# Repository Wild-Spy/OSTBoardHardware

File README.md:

# Open Source Timer Board Hardware
#### Rev 1.1

This repository contains the design for the Open Source Timer board.

These files were created in [KiCad](http://kicad-pcb.org/) 

Rev 1.1 contains
 - Schematic
 - PCB
 - Gerbers
 - BOM
 - PnP File
 - Renders
 - Libs
 - 3D Models

### Latest Version
Latest version is [Rev1.1](https://github.com/Wild-Spy/OSTBoardHardware/tree/rev1.1).  See that tag for more info.

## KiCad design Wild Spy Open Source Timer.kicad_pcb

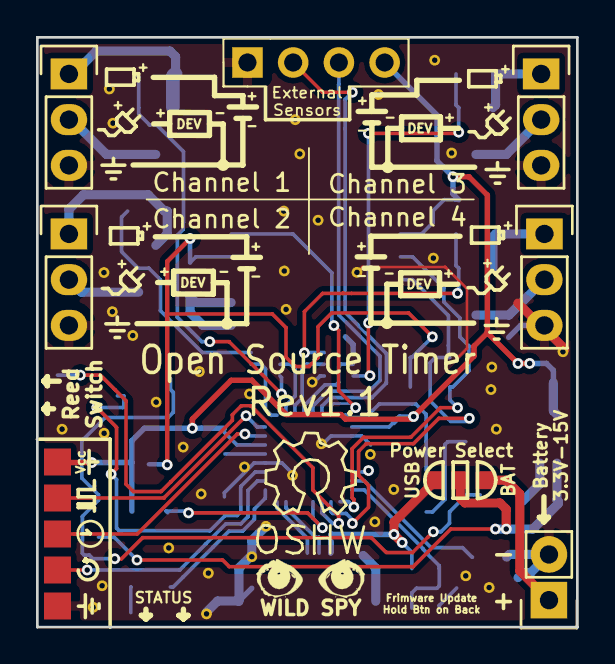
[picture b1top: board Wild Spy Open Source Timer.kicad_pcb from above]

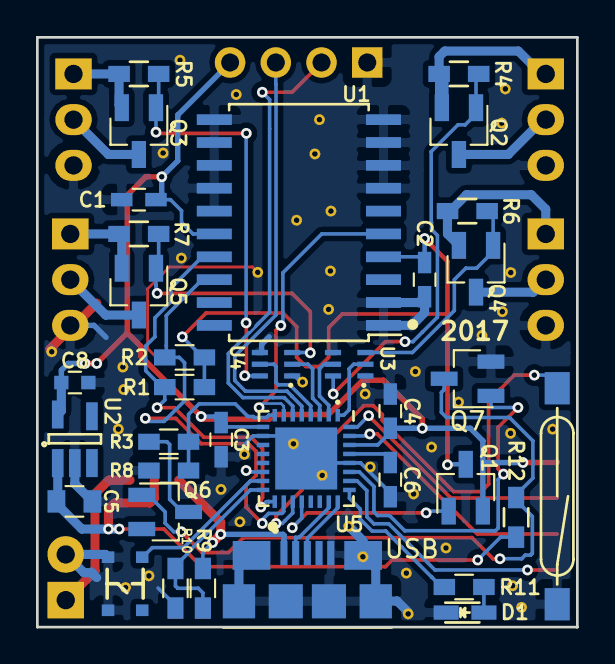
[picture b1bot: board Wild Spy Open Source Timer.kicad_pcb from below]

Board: 2 copper layers, 30.0 x 32.8 mm, 43 parts (35 on the bottom side), 43 nets.

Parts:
Battery1: CONN_01X02; Pin_Header_Straight_1x02
C1, C2, C3, C4: 0.1uF; C_0603_HandSoldering
C5: CL10A105KB8NNNC; C_0805
C6: 1uF; C_0603_HandSoldering
C8: CL10B225KQ8NFNC; C_0603
CH1, CH2, CH3, CH4: CONN_01X03; Pin_Header_Straight_1x03
D1: LED; LED_0603
JP1: JUMPER3; SOLDER-JUMPER_2-WAY
PBus1: CONN_01X04; Pin_Header_Straight_1x04_Pitch2.54mm
Q1, Q2, Q3, Q4, Q5, Q6: AO3415; SOT-23-HandSoldering
Q7: BSH103; SOT-23-HandSoldering
R1, R2, R8: 10k; R_0603_HandSoldering
R3: 150k; R_0603_HandSoldering
R4, R5, R6, R7, R12: 100k; R_0603_HandSoldering
R9, R11: 1k; R_0603_HandSoldering
R10: 2k; R_0603_HandSoldering
SW1: SW_PUSH; KMT071NGJLHS_3x2.6mm_switch
SW2: ORD213; ORD213S-1
SWD1: CONN_01X05; SWD_PROG_HEADER_L
U1: DS3232SN; SOIC-20_7.5x12.8mm_Pitch1.27mm
U2: TPS70933DBVR; SOT-23-5_HandSoldering
U3, U4: UM6K33N; SC88(SOT363)
U5: ATSAMD21E16B; QFN-32-1EP_5x5mm_Pitch0.5mm
USB1: micro_USB

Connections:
+5V: JP1.1, R9.1, USB1.1
/BAT+: Battery1.1, JP1.3
/BL_FW_UPDATE: SW1.1, U5.15
/BatMeasureEn: Q7.1, U5.27
/CH1_EN: U3.2, U5.1
/CH2_EN: U3.5, U5.2
/CH3_EN: U4.2, U5.3
/CH4_EN: U4.5, U5.4
/D+: U5.24, USB1.3
/D-: U5.23, USB1.2
/LED: R11.1, U5.25
/NRESET: SWD1.4, U5.26
/PBus1_MRX: PBus1.2, U5.6
/PBus1_MTX: PBus1.3, U5.5
/REEDSW: SW2.1, U5.19
/RTC_~INT: U1.5, U5.7
/SCL: R2.2, U1.18, U5.18
/SDA: R1.2, U1.17, U5.17
/SWDCLK: SWD1.3, U5.31
/SWDIO: SWD1.2, U5.32
/USBSENSE3.3: R9.2, R10.1, U5.16
/VBat/15: R3.2, R8.1, U5.8
/~RTC_PEN: Q1.1, U5.20
GND: Battery1.2, C1.1, C2.1, C3.2, C4.1, C5.2, C6.1, C8.2, CH1.3, CH2.3, CH3.3, CH4.3, D1.1, PBus1.1, Q7.2, R8.2, R10.2, SW1.2, SW2.2, SWD1.5, U1.1, U1.2, U1.7, U1.8, U1.9, U1.10, U1.11, U1.12, U1.13, U1.14, U1.15, U2.2, U3.1, U3.4, U4.1, U4.4, U5.10, U5.28, U5.33, USB1.5, USB1.6
unnamed: C2.2, Q1.3, R1.1, R2.1, U1.4
unnamed: C6.2, U5.29
unnamed: CH1.1, Q2.2, R4.1
unnamed: CH1.2, Q2.3
unnamed: CH2.1, Q4.2, R6.1
unnamed: CH2.2, Q4.3
unnamed: CH3.1, Q3.2, R5.1
unnamed: CH3.2, Q3.3
unnamed: CH4.1, Q5.2, R7.1
unnamed: CH4.2, Q5.3
unnamed: D1.2, R11.2
unnamed: Q2.1, R4.2, U3.6
unnamed: Q3.1, R5.2, U4.6
unnamed: Q4.1, R6.2, U3.3
unnamed: Q5.1, R7.2, U4.3
unnamed: Q6.1, Q7.3, R12.2
unnamed: Q6.3, R3.1
VAA: C5.1, JP1.2, Q6.2, R12.1, U2.1
VCC: C1.2, C3.1, C4.2, C8.1, PBus1.4, Q1.2, SWD1.1, U1.16, U2.5, U5.9, U5.30

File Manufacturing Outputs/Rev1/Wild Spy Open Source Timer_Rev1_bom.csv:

Component,Description,Part,References,Value,Footprint,Quantity Per PCB,Build Quantity,Datasheet,Supplier 1,Supplier 1 Part Number,Capacitance,Rated Voltage,Temperature Coefficient,Supplier 1 Cost,Tolerance,Supplier 1 Currency,Vdss,Rds(on),Accuracy,Supplier Cost 1,Manufacturer Part Number 1,Supplier Part Number 1,Supplier Currency 1,Manufacturer 1,Type,Switching Current,Manufacturer Part Number
2,Unpolarized capacitor,C_Small,C1 C2 C3 C4,0.1uF,C_0603_HandSoldering,4,400,,,,,,,,,,,,,,,,,,,,
3,Unpolarized capacitor,C_Small,C6,1uF,C_0603_HandSoldering,1,100,,,,,,,,,,,,,,,,,,,,
4,1uF 0805 X5R 50V 10%,CL10A105KB8NNNC,C5,1uF,C_0805,1,100,http://www.samsungsem.com/kr/support/product-search/mlcc/__i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,DigiKey,1276-1860-1-ND,1uF,50V,X5R,0.0653,10%,AUD,,,,,,,,,,,
5,2.2uF 0603 X7R 6.3V 10%,CL10B225KQ8NFNC,C8,2.2uF,C_0603,1,100,http://www.samsungsem.com/kr/front/downloadcms.do?path=/kr/s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,DigiKey,1276-2017-1-ND,2.2uF,6.3V,X7R,0.0337,10%,AUD,,,,,,,,,,,
7,,LED-RESCUE-Wild_Spy_Open_Source_Timer,D1,LED,LED_0603,1,100,,,,,,,,,,,,,,,,,,,,
10,Transistor P-MOSFET (general),Q_PMOS_GSD,Q1 Q2 Q3 Q4 Q5 Q6,AO3415,SOT-23-HandSoldering,6,600,http://aosmd.com/res/data_sheets/AO3415.pdf,DigiKey,785-1010-2-ND,,,,0.11771,,AUD,-20V,53mOhm,,,,,,,,,
11,Resistor,R,R4 R5 R6 R7,100k,R_0603_HandSoldering,4,400,,,,,,,,,,,,,,,,,,,,
12,Resistor,R,R1 R2 R8,10k,R_0603_HandSoldering,3,300,,,,,,,,,,,,5%,,,,,,,,
13,Resistor,R,R3,150k,R_0603_HandSoldering,1,100,,,,,,,,,,,,5%,,,,,,,,
14,Resistor,R,R9 R11,1k,R_0603_HandSoldering,2,200,,,,,,,,,,,,,,,,,,,,
15,Resistor,R,R10,2k,R_0603_HandSoldering,1,100,,,,,,,,,,,,,,,,,,,,
16,NO Reed Switch,ORD213,SW2,ORD213,ORD213S-1,1,100,https://standexelectronics.com/wp-content/uploads/OKI_Reed_S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,Digi Key,,,24 V,,,,,,,,2.07,ORD213S-1-1015,374-1087-ND,AUD,Standex-Meder Electronics,SPST-NO,100mA,
17,Button,SW_PUSH,SW1,SW_PUSH,KMT071NGJLHS_3x2.6mm_switch,1,100,,DigiKey,CKN10291CT-ND,,,,0.39,,AUD,,,,,,,,,,,
19,,ATSAMD21E16B,U5,ATSAMD21E16B,QFN-32-1EP_5x5mm_Pitch0.5mm,1,100,http://www.atmel.com/Images/Atmel-42181-SAM-D21_Datasheet.pdf,DigiKey,1611-ATSAMD21E18A-MUTCT-ND,,,,,,,,,,,,,,,,,ATSAMD21E18A-MUT
20,I2C RTC with Integrated Crystal,DS3232SN,U1,DS3232SN,SOIC-20_7.5x12.8mm_Pitch1.27mm,1,100,http://datasheets.maximintegrated.com/en/ds/DS3232.pdf,DigiKey,DS3232SN#T&RCT-ND,,,,12.4,,AUD,,,,,,,,,,,
21,,TPS70925DBVR,U2,TPS70933DBVR,SOT-23-5_HandSoldering,1,100,http://www.ti.com/lit/ds/symlink/tps709.pdf,DigiKey,296-35483-1-ND,,,,1.19,,AUD,,,,,,,,,,,
22,Dual N Channel MOSFETs,UM6K33N,U3 U4,UM6K33N,SC88(SOT363),2,200,http://rohmfs.rohm.com/en/products/databook/datasheet/discre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,DigiKey,UM6K33NTNTR-ND,,,,0.08638,,AUD,,,,,,,,,,,
23,micro connector,micro_USB,USB1,micro_USB,micro_USB,1,100,http://portal.fciconnect.com/Comergent//fci/drawing/10118192.pdf,DigiKey,609-4613-1-ND,,,,0.4163,,AUD,,,,,,,,,,,
,,,,,,,,,,,,,,,,,,,,,,,,,,,
,,,,,,,,,,,,,,,,,,,,,,,,,,,
,,,,,,,,,,,,,,,,,,,,,,,,,,,
,,,,,,,,,,,,,,,,,,,,,,,,,,,
,,,,,,,,,,,,,,,,,,,,,,,,,,,
Component Groups:,23,,,,,,,,,,,,,,,,,,,,,,,,,,
Component Count:,41,,,,,,,,,,,,,,,,,,,,,,,,,,
Fitted Components:,41,,,,,,,,,,,,,,,,,,,,,,,,,,
Number of PCBs:,100,,,,,,,,,,,,,,,,,,,,,,,,,,
Total components:,4100,,,,,,,,,,,,,,,,,,,,,,,,,,
Schematic Version:,,,,,,,,,,,,,,,,,,,,,,,,,,,
Schematic Date:,,,,,,,,,,,,,,,,,,,,,,,,,,,
BoM Date:,Fri 12 May 2017 20:58:11 AEST,,,,,,,,,,,,,,,,,,,,,,,,,,
Schematic Source:,OSTBoardHardware/Wild Spy Open Source Timer.sch,,,,,,,,,,,,,,,,,,,,,,,,,,
KiCad Version:,Eeschema 4.0.2+dfsg1-stable,,,,,,,,,,,,,,,,,,,,,,,,,,

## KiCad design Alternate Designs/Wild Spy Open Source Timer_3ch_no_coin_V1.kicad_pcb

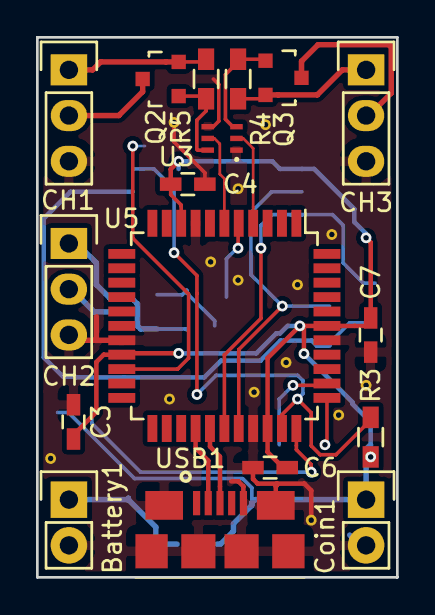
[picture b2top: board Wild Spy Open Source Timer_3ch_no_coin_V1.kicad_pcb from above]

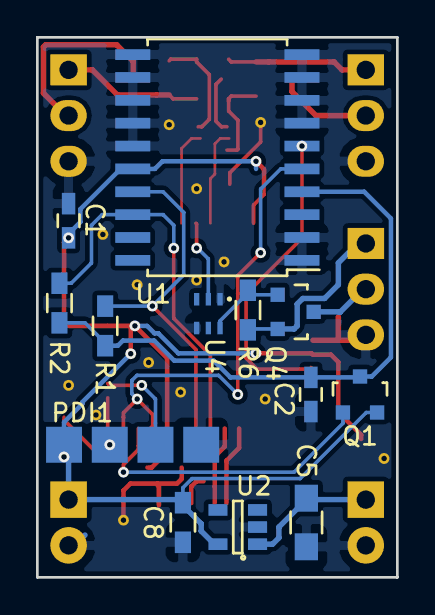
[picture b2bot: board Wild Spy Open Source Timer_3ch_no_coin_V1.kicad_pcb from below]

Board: 2 copper layers, 20.0 x 30.0 mm, 30 parts (13 on the bottom side), 26 nets.

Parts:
Battery1: CONN_01X02; Pin_Header_Straight_1x02
C1, C2, C3, C4, C6, C7: 0.1uF; C_0603_HandSoldering
C5: CL10A105KB8NNNC; R_0805_HandSoldering
C8: CL10B225KQ8NFNC; R_0603_HandSoldering
CH1, CH2, CH3: CONN_01X03; Pin_Header_Straight_1x03
Coin1: CONN_01X02; Pin_Header_Straight_1x02
PDI1: CONN_01X04; PDI_PROG_HEADER
Q1, Q2, Q3, Q4: AO3415; SOT-23
R1, R2, R3, R4, R5, R6: 10k; R_0603_HandSoldering
U1: DS3232SN; SOIC-20_7.5x12.8mm_Pitch1.27mm
U2: TPS70925DBVR; SOT-23-5
U3, U4: UM6K33N; SC88(SOT363)
U5: ATXMEGA32C4-A; TQFP-44_10x10mm_Pitch0.8mm
USB1: micro_USB

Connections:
/CH1_EN: U3.2, U5.4
/CH2_EN: U4.2, U5.5
/CH3_EN: U3.5, U5.6
/CH4_EN: U4.5, U5.7
/D+: U5.27, USB1.3
/D-: U5.26, USB1.2
/PDI_CLK: PDI1.3, U5.35
/PDI_DATA: PDI1.2, U5.34
/RTC_~INT: R3.2, U1.5, U5.32
/SCL: R2.2, U1.18, U5.28
/SDA: R1.2, U1.17, U5.29
/~RST: U1.6, U5.20
/~RTC_PEN: Q1.1, U5.33
GND: Battery1.2, C1.1, C2.1, C3.1, C4.1, C5.2, C6.1, C7.1, C8.2, CH1.3, CH2.3, CH3.3, Coin1.2, PDI1.4, U1.1, U1.2, U1.7, U1.8, U1.9, U1.10, U1.11, U1.12, U1.13, U1.14, U1.15, U2.2, U3.1, U3.4, U4.1, U4.4, U5.8, U5.18, U5.30, U5.38, USB1.5, USB1.6
unnamed: C2.2, Q1.3, R1.1, R2.1, U1.4
unnamed: CH1.1, Q2.2, R4.1
unnamed: CH1.2, Q2.3
unnamed: CH2.1, Q4.2, R6.1
unnamed: CH2.2, Q4.3
unnamed: CH3.1, Q3.2, R5.1
unnamed: CH3.2, Q3.3
unnamed: Q2.1, R4.2, U3.6
unnamed: Q3.1, R5.2, U3.3
unnamed: Q4.1, R6.2, U4.6
VAA: Battery1.1, C5.1, U2.1
VCC: C1.2, C3.2, C4.2, C6.2, C7.2, C8.1, Coin1.1, PDI1.1, Q1.2, R3.1, U1.16, U2.5, U5.9, U5.19, U5.31, U5.39

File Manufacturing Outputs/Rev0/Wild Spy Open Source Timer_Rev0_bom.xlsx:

Component | Description | Part | References | Value | Footprint | Quantity Per PCB | Build Quantity | Datasheet | Config | Supplier 1 | Supplier 1 Part Number | Supplier 1 Cost | Supplier 1 Currency | Capacitance | Rated Voltage | Temperature Coefficient | Tolerance | Vdss | Rds(on) |  | Total Cost
1 | Unpolarized capacitor | C_Small | C1 C2 C3 C4 C6 C7 | 0.1uF | C_0603_HandSoldering | 6 | 600 |  |  | DigiKey | 1276-1012-1-ND | 0.0095 | AUD |  |  |  |  |  |  |  | 5.7
2 | 1uF 0805 X5R 50V 10% | CL10A105KB8NNNC | C5 | 1uF | C_0805 | 1 | 100 | http://www.samsungsem.com/kr/support/product-search/mlcc/__i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 |  | DigiKey | 1276-1860-1-ND | 0.0653 | AUD | 1uF | 50V | X5R | 10% |  |  |  | 6.53
3 | 2.2uF 0603 X7R 6.3V 10% | CL10B225KQ8NFNC | C8 | 2.2uF | C_0603 | 1 | 100 | http://www.samsungsem.com/kr/front/downloadcms.do?path=/kr/s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 |  | DigiKey | 1276-2017-1-ND | 0.0337 | AUD | 2.2uF | 6.3V | X7R | 10% |  |  |  | 3.37
4 | 16mm coin cell holder | 16mm_Coin_Cell | Coin1 | 16mm_Coin_Cell | CoinCell_Holder_1632 | 1 | 100 | http://www.keyelco.com/product-pdf.cfm?p=791 |  | DigiKey | 36-3013-ND | 0.6219 | AUD |  |  |  |  |  |  |  | 62.19
5 | Transistor P-MOSFET (general) | Q_PMOS_GSD | Q1 Q2 Q3 Q4 Q5 | AO3415 | SOT-23 | 5 | 500 | http://aosmd.com/res/data_sheets/AO3415.pdf |  | DigiKey | 785-1010-2-ND | 0.11771 | AUD |  |  |  |  | -20V | 53mOhm |  | 58.855
6 | Resistor | R | R1 R2 R3 R4 R5 R6 R7 | 10k | R_0603_HandSoldering | 7 | 700 |  |  | DigiKey | 311-10KGRCT-ND | 0.006 | AUD |  |  |  |  |  |  |  | 4.2
7 | TQFP44, 16k Flash, 4k Boot, 2k SRAM, 1k EEPROM, JTAG | ATXMEGA32C4-A | U5 | ATXMEGA32C4-A | TQFP-44_10x10mm_Pitch0.8mm | 1 | 100 | http://www.atmel.com/Images/Atmel-8493-8-and-32-bit-AVR-XMEG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 |  | DigiKey | ATXMEGA32C4-AU | 4.1022 | AUD |  |  |  |  |  |  |  | 410.22
8 | I2C RTC with Integrated Crystal | DS3232SN | U1 | DS3232SN | SOIC-20_7.5x12.8mm_Pitch1.27mm | 1 | 100 | http://datasheets.maximintegrated.com/en/ds/DS3232.pdf |  | DigiKey | DS3232SN#T&RCT-ND | 12.4 | AUD |  |  |  |  |  |  |  | 1240
9 |  | TPS70925DBVR | U2 | TPS70925DBVR | SOT-23-5 | 1 | 100 | http://www.ti.com/lit/ds/symlink/tps709.pdf |  | DigiKey | 296-40923-1-ND | 1.1334 | AUD |  |  |  |  |  |  |  | 113.34
10 | Dual N Channel MOSFETs | UM6K33N | U3 U4 | UM6K33N | SC88(SOT363) | 2 | 200 | http://rohmfs.rohm.com/en/products/databook/datasheet/discre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 |  | DigiKey | UM6K33NTNTR-ND | 0.08638 | AUD |  |  |  |  |  |  |  | 17.276
11 | micro connector | micro_USB | USB1 |  | micro_USB | 1 | 100 | http://portal.fciconnect.com/Comergent//fci/drawing/10118192.pdf |  | DigiKey | 609-4613-1-ND | 0.4163 | AUD |  |  |  |  |  |  |  | 41.63
 |  |  |  |  |  |  |  |  |  |  |  |  |  |  |  |  |  |  |  |  | 1963.311
 |  |  |  |  |  |  |  |  |  |  |  |  |  |  |  |  |  |  |  |  | 19.63311
Component Groups: | 16
Component Count: | 36
Fitted Components: | 27
Number of PCBs: | 100
Total components: | 2700
Schematic Version:
Schematic Date:
BoM Date: | Sat 12 Nov 2016 16:17:47 AEDT
Schematic Source: | Wild Spy Open Source Timer.sch
KiCad Version: | Eeschema 4.0.2+dfsg1-stable

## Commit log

2017-04-30 Initial commit with Rev0 design.
2017-04-30 Restructure, clean up.
2017-05-02 Swapped to the d21 in the schematic
2017-05-08 - Updates to Rev1 Schematic - Organising/Tidying - Add peripheral bus port - Battery voltage measurement - Battery/USB selection jumper - Started skeleton of Rev1 PCB - Added libs folder with some fo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
2017-05-09 PCB components placed
2017-05-09 Routing for the Timer PCB- almost done
2017-05-11 Cleaned up routing on PCB a bit. Made some changes to schematic, added a few things.
2017-05-11 Pretty much finished REV1 PCB. Just need to have a quick look over it and export gerbers etc.
2017-05-12 Finished the PCB layout
2017-05-12 Generated Gerbers for Rev1 Generated BOM for Rev1 Generated renders for Rev1 Some updating of paths and libs
2017-05-12 Update readme Update Rev1 renders
2017-05-12 Fixed bug in library - wrong 3d model for USB Fixed Front layer silkscreen - had no battery reference of voltage range Regenerated Gerbers Regenerated renders
2017-05-22 The schematic for the wav trigger board. Needs checking. No rats nesting done yet
2017-05-22 Updated with comments and footprints for the headers
2017-07-22 Removed Harry's commit of WavTriggerBoard. Should not be in this repo. Updated chip in schematic.
2017-08-08 Fixed battery volrage measurement issue in hardware.
2017-08-13 Manufacturing outputs for Rev1.1
2017-08-13 Clean up
